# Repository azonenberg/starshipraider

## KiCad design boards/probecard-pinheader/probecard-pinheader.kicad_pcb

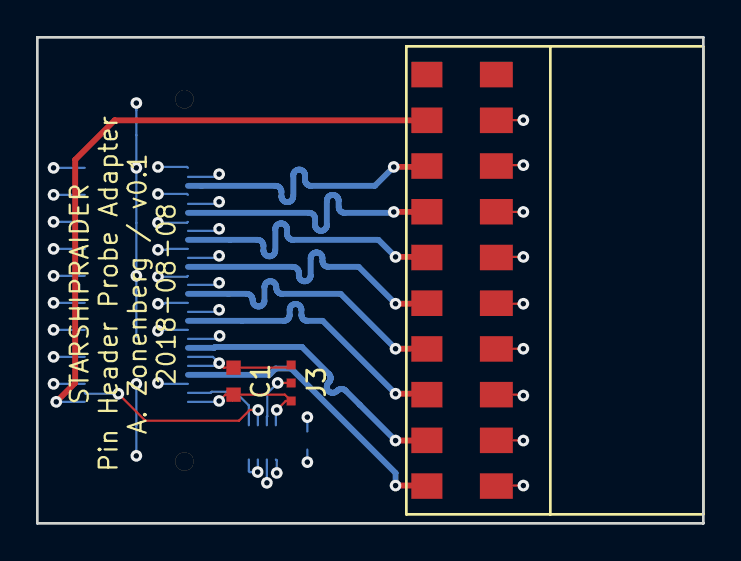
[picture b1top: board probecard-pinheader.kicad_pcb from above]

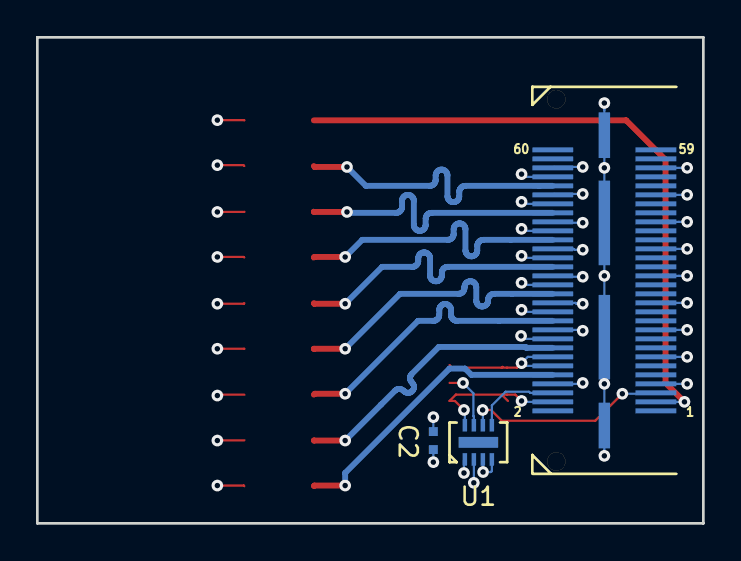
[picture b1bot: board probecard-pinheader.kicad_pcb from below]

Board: 4 copper layers, 37.0 x 27.0 mm, 6 parts (3 on the bottom side), 14 nets.

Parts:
C1: 4.7 uF; EIA_0603_CAP_NOSILK
C2: 0.47 uF; EIA_0402_CAP_NOSILK
J1: STARSHIPRAIDER_PROBE_MODULE; CONN_SAMTEC_QSH-030-01-L-D-A
J2: STARSHIPRAIDER_PINHDR; CONN_SAMTEC_SMH_110_02_L_D
J3: JUMPER_0402_SPDT; EIA_0402_JUMPER
U1: 24C04-DFN8; DFN_8_0.5MM_2x3MM

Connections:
/3V3: C1.1, C2.1, J1.4, J3.1, U1.2, U1.8
/DQ0: J1.10, J2.1
/DQ1: J1.16, J2.3
/DQ2: J1.22, J2.5
/DQ3: J1.28, J2.7
/DQ4: J1.34, J2.9
/DQ5: J1.40, J2.11
/DQ6: J1.46, J2.13
/DQ7: J1.52, J2.15
/EEPROM_WP_N: J3.2, U1.7
/GND: C1.2, C2.2, J1.7, J1.8, J1.12, J1.13, J1.14, J1.18, J1.19, J1.20, J1.24, J1.25, J1.26, J1.30, J1.31, J1.32, J1.36, J1.37, J1.38, J1.42, J1.43, J1.44, J1.48, J1.49, J1.50, J1.54, J1.55, J1.56, J1.GND, J2.2, J2.4, J2.6, J2.8, J2.10, J2.12, J2.14, J2.16, J2.18, J3.3, U1.1, U1.3, U1.4
/I2C_SCL: J1.5, U1.6
/I2C_SDA: J1.6, U1.5
/VCCO_REF: J1.3, J2.17

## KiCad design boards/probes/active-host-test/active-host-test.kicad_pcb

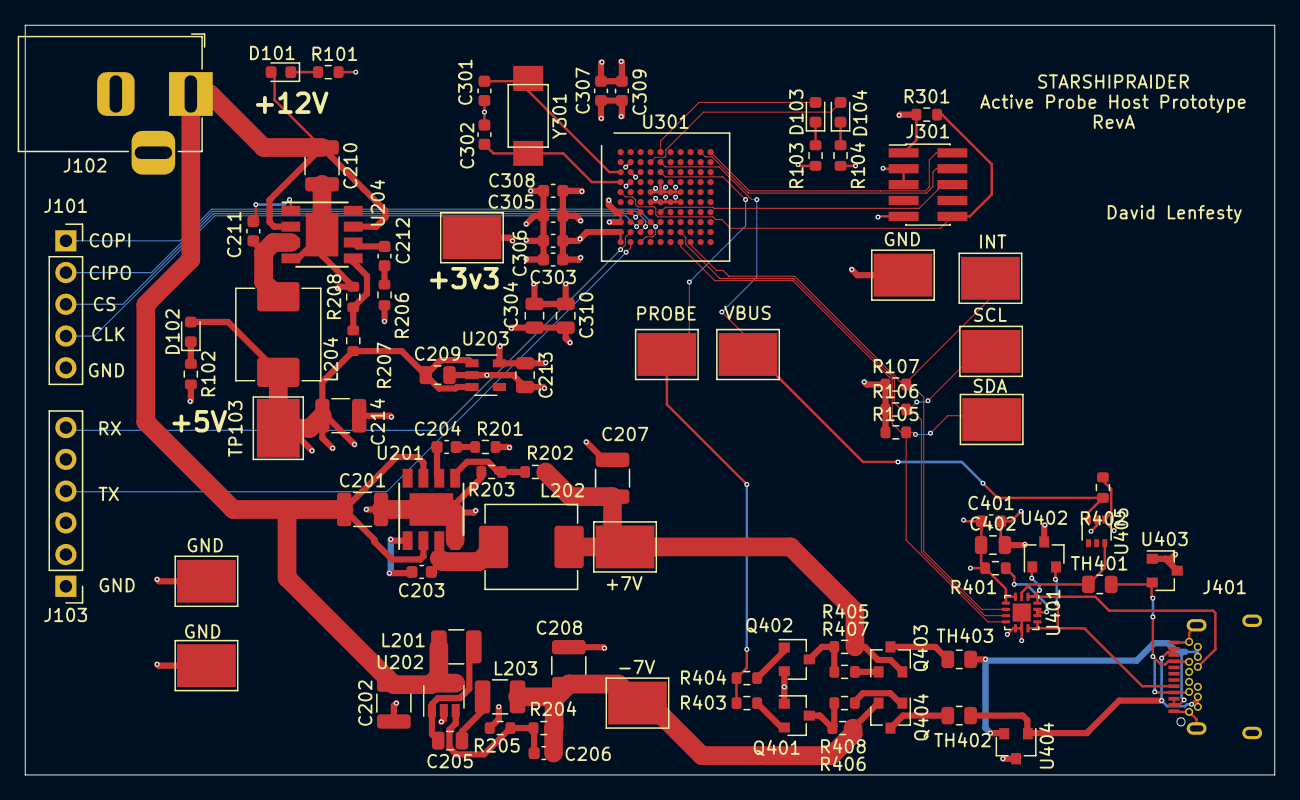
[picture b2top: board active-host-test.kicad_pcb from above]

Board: 4 copper layers, 100.0 x 60.0 mm, 93 parts (0 on the bottom side), 57 nets.

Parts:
C201, C202, C208, C210: 22u; C_1210_3225Metric
C203, C211, C306: 10n; C_0603_1608Metric
C204, C212: 6n8; C_0603_1608Metric
C205, C209, C213, C304, C310, C402: 1u; C_0805_2012Metric
C206: 330p; C_0603_1608Metric
C207, C214: 47u; C_1210_3225Metric
C301, C302: 10p; C_0603_1608Metric
C303, C305, C307, C308, C309, C401: 0u1; C_0603_1608Metric
D101, D102, D103, D104: LED; LED_0603_1608Metric
J101: Conn_01x05_Male; PinSocket_1x05_P2.54mm_Vertical
J102: Barrel_Jack; BarrelJack_Horizontal
J103: Conn_01x06_Male; PinHeader_1x06_P2.54mm_Vertical
J301: Conn_ARM_JTAG_SWD_10; PinHeader_2x05_P1.27mm_Vertical_SMD
J401: USB_C_Receptacle; 10137062
L201, L203: 22u; L_1210_3225Metric
L202, L204: 12u; L_Abracon_ASPI-0630LR
Q401: Q_PNP_BEC; SOT-23
Q402: Q_NPN_BEC; SOT-23
Q403: Q_PMOS_GSD; SOT-23
Q404: Q_NMOS_GSD; SOT-23
R101, R102, R105, R106, R107, R203, R205, R208, R301, R402, R403, R404, R405, R406: 10k; R_0603_1608Metric
R103, R104: 1k; R_0603_1608Metric
R201, R206: 6k8; R_0603_1608Metric
R202: 66k; R_0603_1608Metric
R204: 47k; R_0603_1608Metric
R207: 44k; R_0603_1608Metric
R401: 0R; R_0603_1608Metric
R407, R408: 100R; R_0603_1608Metric
TH401, TH402, TH403: Thermistor_PTC; R_0805_2012Metric
TP101, TP102, TP103, TP104, TP105, TP106, TP107, TP108, TP109, TP110, TP111, TP112: TestPoint; Keystone_5016
U201, U204: AP6502; Diodes_SO-8EP
U202: LM2611xMF; SOT-23-5
U203: AP2112K-3.3; SOT-23-5
U301: STM32F103V8Hx; LFBGA-100_10x10mm_Layout10x10_P0.8mm
U401: FUSB302BMPX; WQFN-14-1EP_2.5x2.5mm_P0.5mm_EP1.45x1.45mm
U402: STS232033B102; SOT-23
U403: STS232050B751; SOT-23
U404: STS232120B301; SOT-23
U405: LM66100; SOT-363_SC-70-6
Y301: 8MHz; Crystal_NX5032

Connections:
+3V3: C213.1, C303.1, C304.1, C305.1, C306.1, C307.1, C308.1, C309.1, C310.1, J301.1, R105.1, R106.1, R107.1, R301.1, TP104.1, U203.5, U301.B2, U301.D2, U301.F4, U301.F5, U301.F6, U301.F7, U301.J1, U301.K1
+5V: C209.1, C214.1, C401.1, C402.1, D102.2, L204.2, R207.1, R401.1, R402.1, TP103.1, U203.1, U203.3, U401.3, U401.4, U405.1
/+7V: C207.1, L202.2, Q403.2, R202.1, R405.1, TP101.1
/+12V: C201.1, C202.1, C210.1, D101.2, J102.1, L201.1, U201.2, U201.7, U202.4, U202.5, U204.2, U204.7
/-7V: C206.1, C208.1, L203.2, Q404.2, R204.1, R406.2, TP102.1
/I2C_SCL: R106.2, TP108.1, U301.J7, U401.6
/I2C_SDA: R105.2, TP107.1, U301.K7, U401.7
/I2C_~INT: R107.2, TP109.1, U301.K8, U401.5
/MCU/NRST: J301.10, R301.2, U301.E1
/MCU/SWCLK: J301.4, U301.A9
/MCU/SWDIO: J301.2, U301.A10
/MCU/SWO: J301.6, U301.G5
/MCU/UART_RX: J103.4, U301.K2
/MCU/UART_TX: J103.6, U301.J2
/PROBE_PWR_EN: R403.2, R404.2, TP105.1, U301.C5
/PROBE_VBUS_~EN: R402.2, TP106.1, U301.B5, U405.3
/SPI_CIPO: J101.2, U301.J3
/SPI_CLK: J101.4, U301.H3
/SPI_COPI: J101.1, U301.K3
/SPI_~CS: J101.3, U301.G3
/USB C/+7V_FUSED: J401.A2, J401.A3, J401.B2, J401.B3, TH403.1, U404.2
/USB C/+7V_GATED: Q403.3, TH403.2
/USB C/-7V_FUSED: J401.A10, J401.A11, J401.B10, J401.B11, TH402.2, U404.1
/USB C/-7V_GATED: Q404.3, TH402.1
/USB C/CC1: J401.A5, U401.10, U401.11, U402.2
/USB C/CC2: J401.B5, U401.1, U401.14, U402.1
/USB C/VBUS: TH401.1, U401.2, U405.6
/USB C/VBUS_FUSED: J401.A4, J401.A9, J401.B4, J401.B9, TH401.2, U403.2
/USRLED1: D103.2, U301.A5
/USRLED2: D104.2, U301.B4
GND: C201.2, C202.2, C207.2, C208.2, C209.2, C210.2, C213.2, C214.2, C301.2, C302.2, C303.2, C304.2, C305.2, C306.2, C307.2, C308.2, C309.2, C310.2, C401.2, C402.2, J101.5, J102.2, J103.1, J301.3, J301.5, J301.9, J401.A1, J401.A12, J401.B1, J401.B12, J401.S1, Q401.1, Q402.2, R101.2, R102.2, R103.2, R104.2, R201.2, R203.2, R205.2, R206.2, R208.2, TP110.1, TP111.1, TP112.1, U201.4, U201.9, U202.2, U203.2, U204.4, U204.9, U301.C2, U301.D5, U301.E4, U301.E5, U301.E6, U301.E7, U301.G1, U301.H1, U401.8, U401.9, U401.15, U402.3, U403.1, U403.3, U404.3, U405.2
unnamed: C203.1, U201.1
unnamed: C203.2, L202.1, U201.3
unnamed: C204.1, U201.6
unnamed: C204.2, R201.1
unnamed: C205.1, L203.1
unnamed: C205.2, L201.2, U202.1
unnamed: C206.2, R204.2, R205.1, U202.3
unnamed: C211.1, U204.1
unnamed: C211.2, L204.1, U204.3
unnamed: C212.1, U204.6
unnamed: C212.2, R206.1
unnamed: C301.1, U301.C1, Y301.1
unnamed: C302.1, U301.D1, Y301.2
unnamed: D101.1, R101.1
unnamed: D102.1, R102.1
unnamed: D103.1, R103.1
unnamed: D104.1, R104.1
unnamed: Q401.2, R403.1
unnamed: Q401.3, R406.1, R408.2
unnamed: Q402.1, R404.1
unnamed: Q402.3, R405.2, R407.2
unnamed: Q403.1, R407.1
unnamed: Q404.1, R408.1
unnamed: R202.2, R203.1, U201.5
unnamed: R207.2, R208.1, U204.5
unnamed: R401.2, U401.12, U401.13

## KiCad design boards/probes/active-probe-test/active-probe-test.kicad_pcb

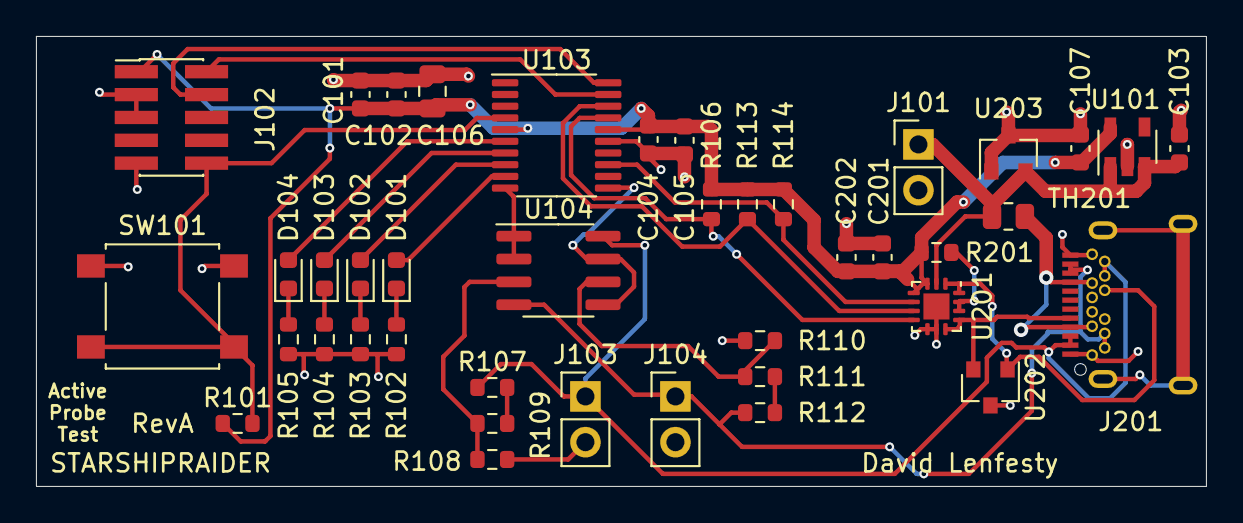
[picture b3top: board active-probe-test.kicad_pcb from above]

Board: 2 copper layers, 65.0 x 25.0 mm, 41 parts (0 on the bottom side), 29 nets.

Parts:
C101, C103, C104, C107, C201: 0u1; C_0603_1608Metric
C102: 10n; C_0603_1608Metric
C105, C202: 1u; C_0603_1608Metric
C106: 4u7; C_0805_2012Metric
D101, D102, D103, D104: LED; LED_0603_1608Metric
J101, J103, J104: Conn_01x02_Male; PinHeader_1x02_P2.54mm_Vertical
J102: Conn_ARM_JTAG_SWD_10; PinHeader_2x05_P1.27mm_Vertical_SMD
J201: USB_C_Receptacle; 10137062
R101, R106, R107, R108, R109, R110, R111, R112, R113, R114: 10k; R_0603_1608Metric
R102, R103, R104, R105: 1k; R_0603_1608Metric
R201: 0R; R_0603_1608Metric
SW101: SW_Push; SW_SPST_B3S-1000
TH201: Thermistor_PTC; R_0805_2012Metric
U101: AP2112K-3.3; SOT-23-5
U103: STM32F042F6Px; TSSOP-20_4.4x6.5mm_P0.65mm
U104: LM358; SOIC-8_3.9x4.9mm_P1.27mm
U201: FUSB302BMPX; WQFN-14-1EP_2.5x2.5mm_P0.5mm_EP1.45x1.45mm
U202: STS232033B102; SOT-23
U203: STS232050B751; SOT-23

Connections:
+3V3: C101.1, C102.1, C104.1, C105.1, C106.1, C107.1, C201.1, C202.1, J102.1, R101.1, R106.1, R113.1, R114.1, R201.1, U101.5, U103.5, U103.16, U201.3, U201.4
/+7V: J103.1, J201.A2, J201.A3, J201.B2, J201.B3, R107.1, U104.8
/+7V_SENSE: U103.10, U104.1, U104.2
/-7V: J104.1, J201.A10, J201.A11, J201.B10, J201.B11, R112.2, U104.4
/-7V_SENSE: U103.11, U104.5, U104.7
/FUSB_INT: R114.2, U103.13, U201.5
/I2C1_SCL: R106.2, U103.17, U201.7
/I2C1_SDA: R113.2, U103.18, U201.6
/NRST: J102.10, R101.2, SW101.2, U103.4
/SWCLK: J102.4, U103.20
/SWDIO: J102.2, U103.19
/USB/CC1: J201.A5, U201.10, U201.11, U202.2
/USB/CC2: J201.B5, U201.1, U201.14, U202.1
/USB/VBUS_RAW: J201.A4, J201.A9, J201.B4, J201.B9, TH201.2
/USRLED1: D104.2, U103.6
/USRLED2: D103.2, U103.7
/USRLED3: D102.2, U103.8
/USRLED4: D101.2, U103.9
/VBUS: C103.1, J101.1, TH201.1, U101.1, U101.3, U201.2, U203.2
GND: C101.2, C102.2, C103.2, C104.2, C105.2, C106.2, C107.2, C201.2, C202.2, J101.2, J102.3, J102.5, J102.9, J103.2, J104.2, J201.A1, J201.A12, J201.B1, J201.B12, R102.2, R103.2, R104.2, R105.2, R109.2, R110.1, SW101.1, U101.2, U103.15, U201.8, U201.9, U201.15, U202.3, U203.1, U203.3
unnamed: D101.1, R102.1
unnamed: D102.1, R103.1
unnamed: D103.1, R104.1
unnamed: D104.1, R105.1
unnamed: R107.2, R108.1
unnamed: R108.2, R109.1, U104.3
unnamed: R110.2, R111.1, U104.6
unnamed: R111.2, R112.1
unnamed: R201.2, U201.12, U201.13

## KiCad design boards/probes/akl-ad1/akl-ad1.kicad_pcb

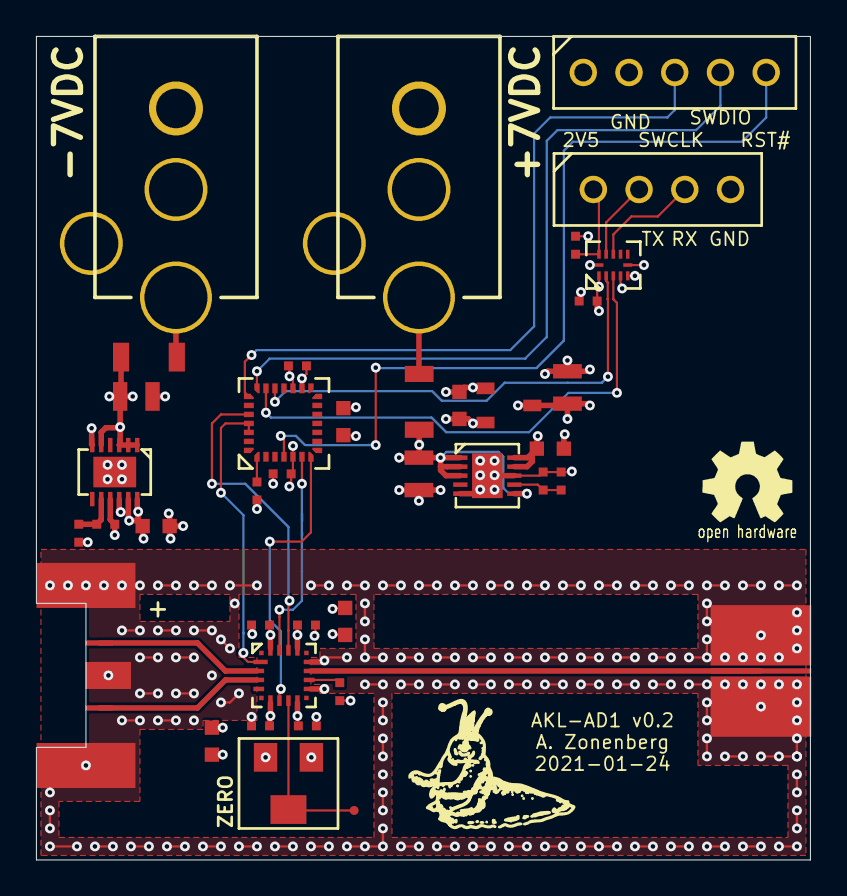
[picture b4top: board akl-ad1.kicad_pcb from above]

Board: 4 copper layers, 43.0 x 45.8 mm, 39 parts (0 on the bottom side), 28 nets.

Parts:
C3, C4, C14, C15, C16, C17: 4.7 uF; EIA_0603_CAP_NOSILK
C5, C6, C7, C8, C12, C13, C18, C19, C20, C21: 0.47 uF; EIA_0402_CAP_NOSILK
C9, C10, C11: 4.7 uF 16V; EIA_0805_CAP_NOSILK
J1: 3211-60087; CONN_SMPM_DUAL_AMPHENOL_3211-60087
J2: 901-10511-3; CONN_SMA_EDGE_AMPHENOL_901_10511_3
J3: TESTPOINT; TESTPOINT_SMT_0.5MM
J4, J5: BARREL; CONN_CUI_PJ-058BH_HIPWR_BARREL_NOSLOT
J6: Conn_01x05; CONN_HEADER_2.54MM_1x5
J7: Conn_01x04; CONN_HEADER_2.54MM_1x4
L1, L2: BLM31KN271SH1L; EIA_1206_CAP_NOSILK
R1: 49.9; EIA_0402_RES_NOSILK
R2, R3: 24.9K; EIA_0402_CAP_NOSILK
R4: 10K; EIA_0402_RES_NOSILK
RV1: SM-43TW103; TRIMPOT_NIDEC_SM4xW
U1: LMH6401; QFN_16_0.5MM_3x3MM_TI_RMZ
U2: LT3042; DFN_10_0.5MM_3x3MM
U3: LT3093; DFN_12_0.5MM_3x3MM
U4: MCP1703T-2502E/CB; SOT23_3
U5: STM32F031-QFN28; QFN_28_0.5MM_4x4MM_NOPAD
U6: TXB0104RUT; QFN_12_0.4MM_2x1.7MM_TI_RUT

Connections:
/2V5_D: C16.1, C17.1, C18.1, C19.1, C21.1, J6.1, U4.2, U5.5, U5.17, U6.1, U6.12
/2V5_N: C4.2, C6.2, C8.2, C15.1, RV1.3, U1.5, U1.16, U3.10, U3.11, U3.12
/2V5_P: C3.1, C5.1, C7.1, C14.1, RV1.1, U1.8, U1.13, U2.9, U2.10
/AMP_CS_N: U1.15, U5.6
/AMP_PD: U1.6, U5.7
/GND: C3.2, C4.1, C5.2, C6.1, C7.2, C8.1, C9.2, C10.2, C11.2, C12.2, C13.2, C14.2, C15.2, C16.2, C17.2, C18.2, C19.2, C20.2, C21.2, J1.3, J2.2, J4.2, J5.2, J6.2, J7.4, R1.2, R2.2, R3.2, R4.2, U1.9, U1.12, U2.5, U2.8, U2.PAD, U3.6, U3.9, U4.1, U5.16, U6.4, U6.5, U6.6
/IN_N: J1.2, U1.3
/IN_P: J1.1, U1.2
/MCU/MCU_RST_N: J6.5, U5.4
/MCU/SWCLK: J6.3, U5.22
/MCU/SWDIO: J6.4, U5.21
/MCU/UART_RX: U5.20, U6.3
/MCU/UART_RX_VOUT: J7.3, U6.9
/MCU/UART_TX: U5.19, U6.2
/MCU/UART_TX_VOUT: J7.2, U6.10
/MCU/VCCIO_UART: C20.1, J7.1, U6.11
/Power Supply/7V0_N: C10.1, L2.1, U3.1, U3.2, U3.3, U3.5, U3.PAD
/Power Supply/7V0_P: C9.1, C11.1, L1.1, U2.1, U2.2, U2.3, U2.6, U4.3
/SPI_SCK: U1.14, U5.24
/SPI_SDIO: U1.1, U5.25, U5.26
/VOCM: J3.1, RV1.2, U1.7
/VOUT: J2.1, U1.11
unnamed: C12.1, R2.1, U2.7
unnamed: C13.1, R3.1, U3.8
unnamed: J4.1, L1.2
unnamed: J5.1, L2.2
unnamed: R1.1, U1.10
unnamed: R4.1, U5.1

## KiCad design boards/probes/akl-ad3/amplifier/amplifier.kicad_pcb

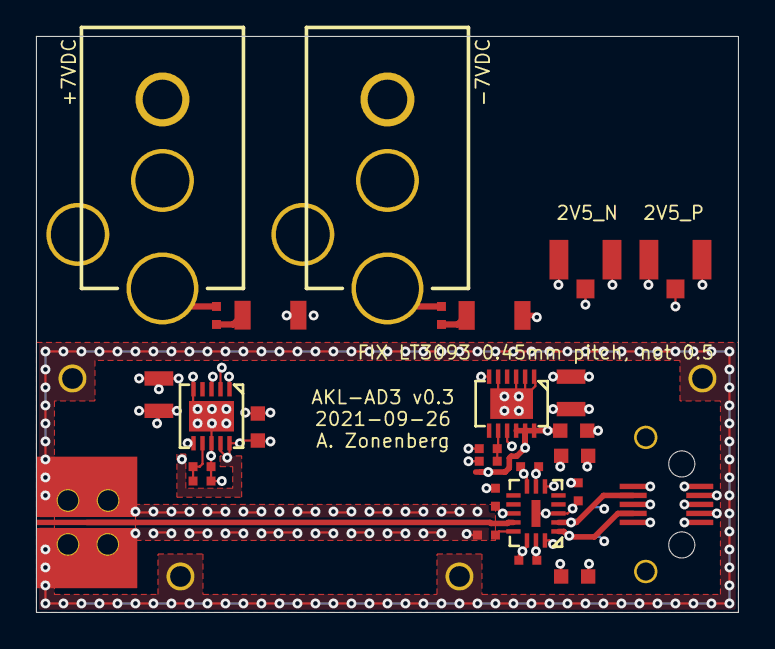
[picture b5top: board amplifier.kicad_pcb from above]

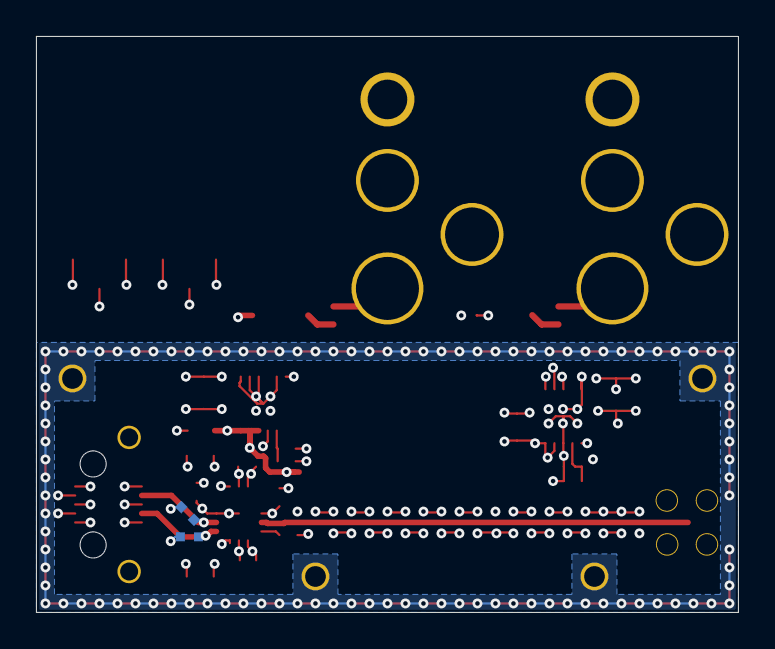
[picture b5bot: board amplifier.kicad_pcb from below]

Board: 4 copper layers, 39.0 x 32.0 mm, 34 parts (2 on the bottom side), 15 nets.

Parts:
C1, C2: 4.7 uF 16V; EIA_0805_CAP_NOSILK
C3, C4, C9, C10, C11, C12: 0.47 uF; EIA_0402_CAP_NOSILK
C5, C6, C7, C8: 4.7 uF; EIA_0603_CAP_NOSILK
F1, F2: 1A; EIA_0402_RES_NOSILK
J1, J2: CONN_3_PWROUT; CONN_CUI_PJ-058BH_HIPWR_BARREL_NOSLOT
J3: 901-10510-2; CONN_SMA_EDGE_AMPHENOL_901_10510-2
J4, J5: U.FL; CONN_U.FL_TE_1909763-1
J6: LSHM-105-02.5-L-DV-A-S-K-TR; CONN_SAMTEC_LSHM-105-02.5-L-DV-A-S-K-TR
L1, L2: BLM31KN271SH1L; EIA_1206_CAP_NOSILK
MH1, MH2, MH3, MH4: 1MM; MECHANICAL_CLEARANCEHOLE_M1
R1, R2: 24.9K; EIA_0402_RES_NOSILK
R3: 49.9; EIA_0402_RES_NOSILK
R4, R5: 110; EIA_0402_RES_NOSILK
U1: LT3042; DFN_10_0.5MM_3x3MM
U2: LT3093; DFN_12_0.5MM_3x3MM
U3: ADL5569; QFN_16_0.5MM_2.5x3MM

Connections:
/2V5_N: C6.1, C8.1, C10.1, C12.1, J5.1, U2.10, U2.11, U2.12, U3.3, U3.6, U3.11, U3.PAD
/2V5_P: C5.1, C7.1, C9.1, C11.1, J4.1, U1.9, U1.10, U3.8, U3.14, U3.16
/7V0_N: C2.1, L2.1, U2.1, U2.2, U2.3, U2.5, U2.PAD
/7V0_P: C1.1, L1.1, U1.1, U1.2, U1.3, U1.6
/GND: C1.2, C2.2, C3.2, C4.2, C5.2, C6.2, C7.2, C8.2, C9.2, C10.2, C11.2, C12.2, J1.2, J2.2, J3.2, J4.2, J5.2, J6.1, J6.2, J6.4, J6.5, J6.6, J6.8, J6.9, J6.10, J6.SHLD, MH1.1, MH2.1, MH3.1, MH4.1, R1.2, R2.2, R3.2, R4.2, R5.2, U1.5, U1.8, U1.PAD, U2.6, U2.9, U3.7, U3.15
/VIN_N: J6.3, R5.1, U3.1
/VIN_P: J6.7, R4.1, U3.2
/VOUT: J3.1, U3.12
unnamed: C3.1, R1.1, U1.7
unnamed: C4.1, R2.1, U2.8
unnamed: F1.1, J1.1
unnamed: F1.2, L1.2
unnamed: F2.1, J2.1
unnamed: F2.2, L2.2
unnamed: R3.1, U3.13

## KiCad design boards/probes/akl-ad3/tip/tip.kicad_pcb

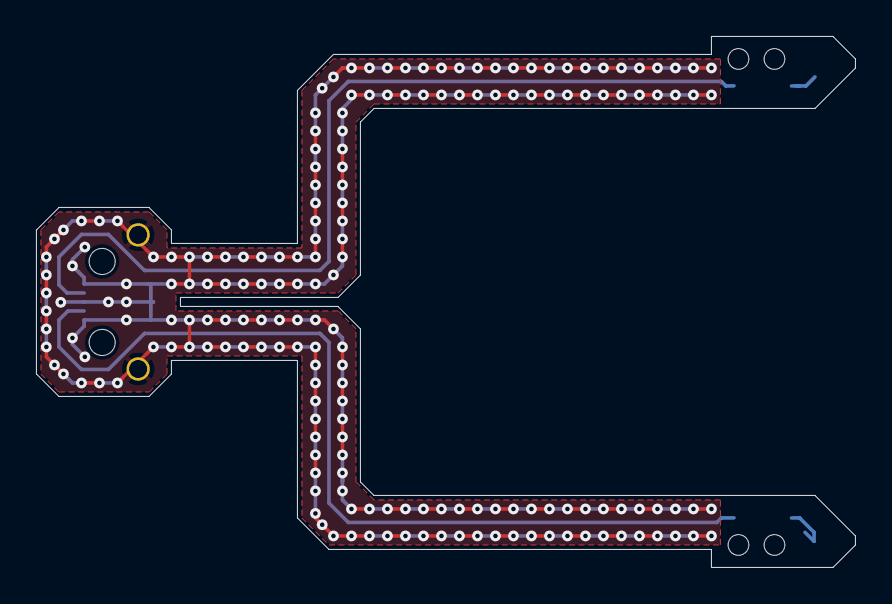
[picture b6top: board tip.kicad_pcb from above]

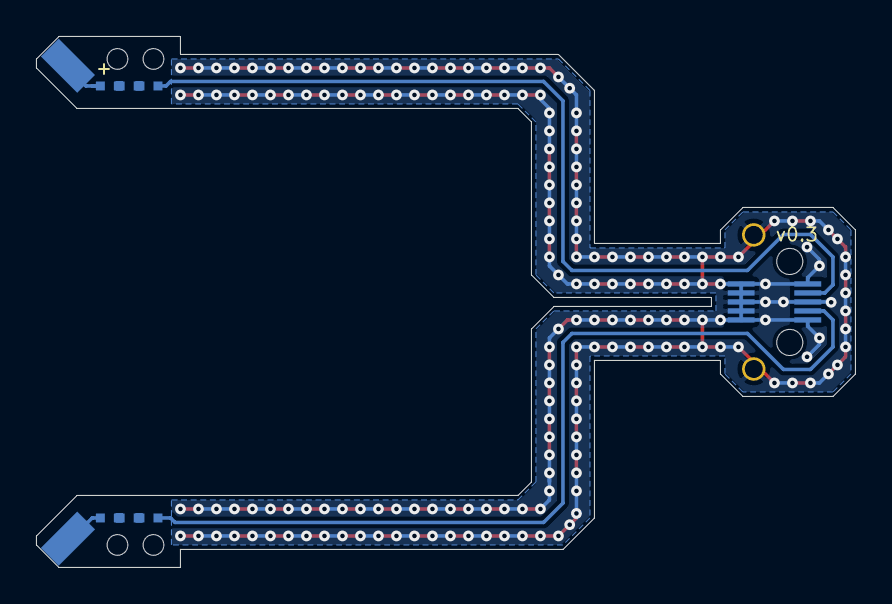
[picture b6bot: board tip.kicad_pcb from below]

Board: 2 copper layers, 45.5 x 29.5 mm, 9 parts (9 on the bottom side), 9 nets.

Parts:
J1: Conn_01x10_shielded; CONN_SAMTEC_LSHM-105-02.5-L-DV-A-S-K-TR
J2, J3: SOCKET; CONN_TE_2-331677-6_EDGELAUNCH
R1, R2: FC0402E50R0BTT0; EIA_0402_RES_NOSILK_FLIPCHIP
R3, R4, R5, R6: FC0402E2000BTT0; EIA_0402_RES_NOSILK_FLIPCHIP

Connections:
/GND: J1.1, J1.2, J1.3, J1.5, J1.6, J1.7, J1.9, J1.10, J1.SHLD
/IN_N: J3.1, R6.1
/IN_P: J2.1, R5.1
/IN_R_N: J1.4, R2.2
/IN_R_P: J1.8, R1.2
unnamed: R1.1, R3.2
unnamed: R2.1, R4.2
unnamed: R3.1, R5.2
unnamed: R4.1, R6.2

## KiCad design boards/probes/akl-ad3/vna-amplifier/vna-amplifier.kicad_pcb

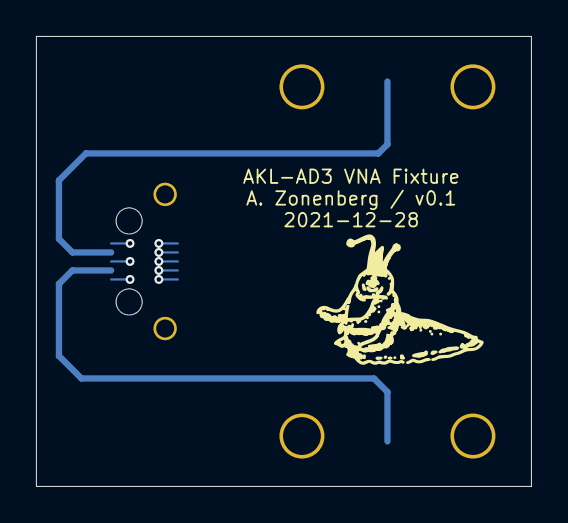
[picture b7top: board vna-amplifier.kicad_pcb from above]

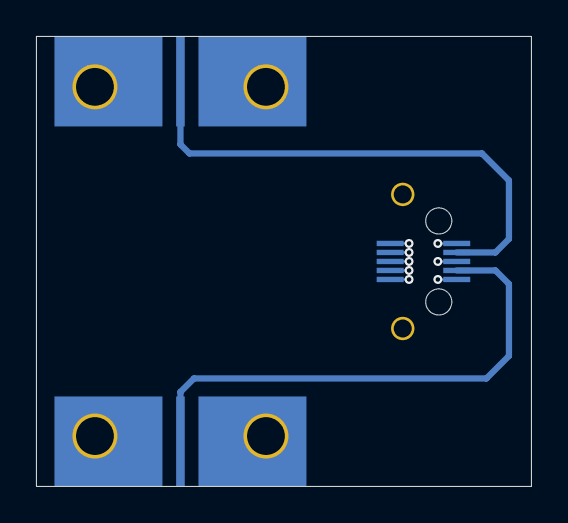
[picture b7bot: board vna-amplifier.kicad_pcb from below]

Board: 4 copper layers, 27.5 x 25.0 mm, 3 parts (3 on the bottom side), 3 nets.

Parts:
J1: Conn_01x10_shielded; CONN_SAMTEC_LSHM-105-02.5-L-DV-A-S-K-TR
J2, J3: 32K243-40ML5; CONN_SMA_EDGE_ROSENBERGER_32K243_40ML5

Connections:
/GND: J1.1, J1.2, J1.3, J1.5, J1.6, J1.7, J1.9, J1.10, J1.SHLD, J2.2, J3.2
/IN_R_N: J1.4, J2.1
/IN_R_P: J1.8, J3.1

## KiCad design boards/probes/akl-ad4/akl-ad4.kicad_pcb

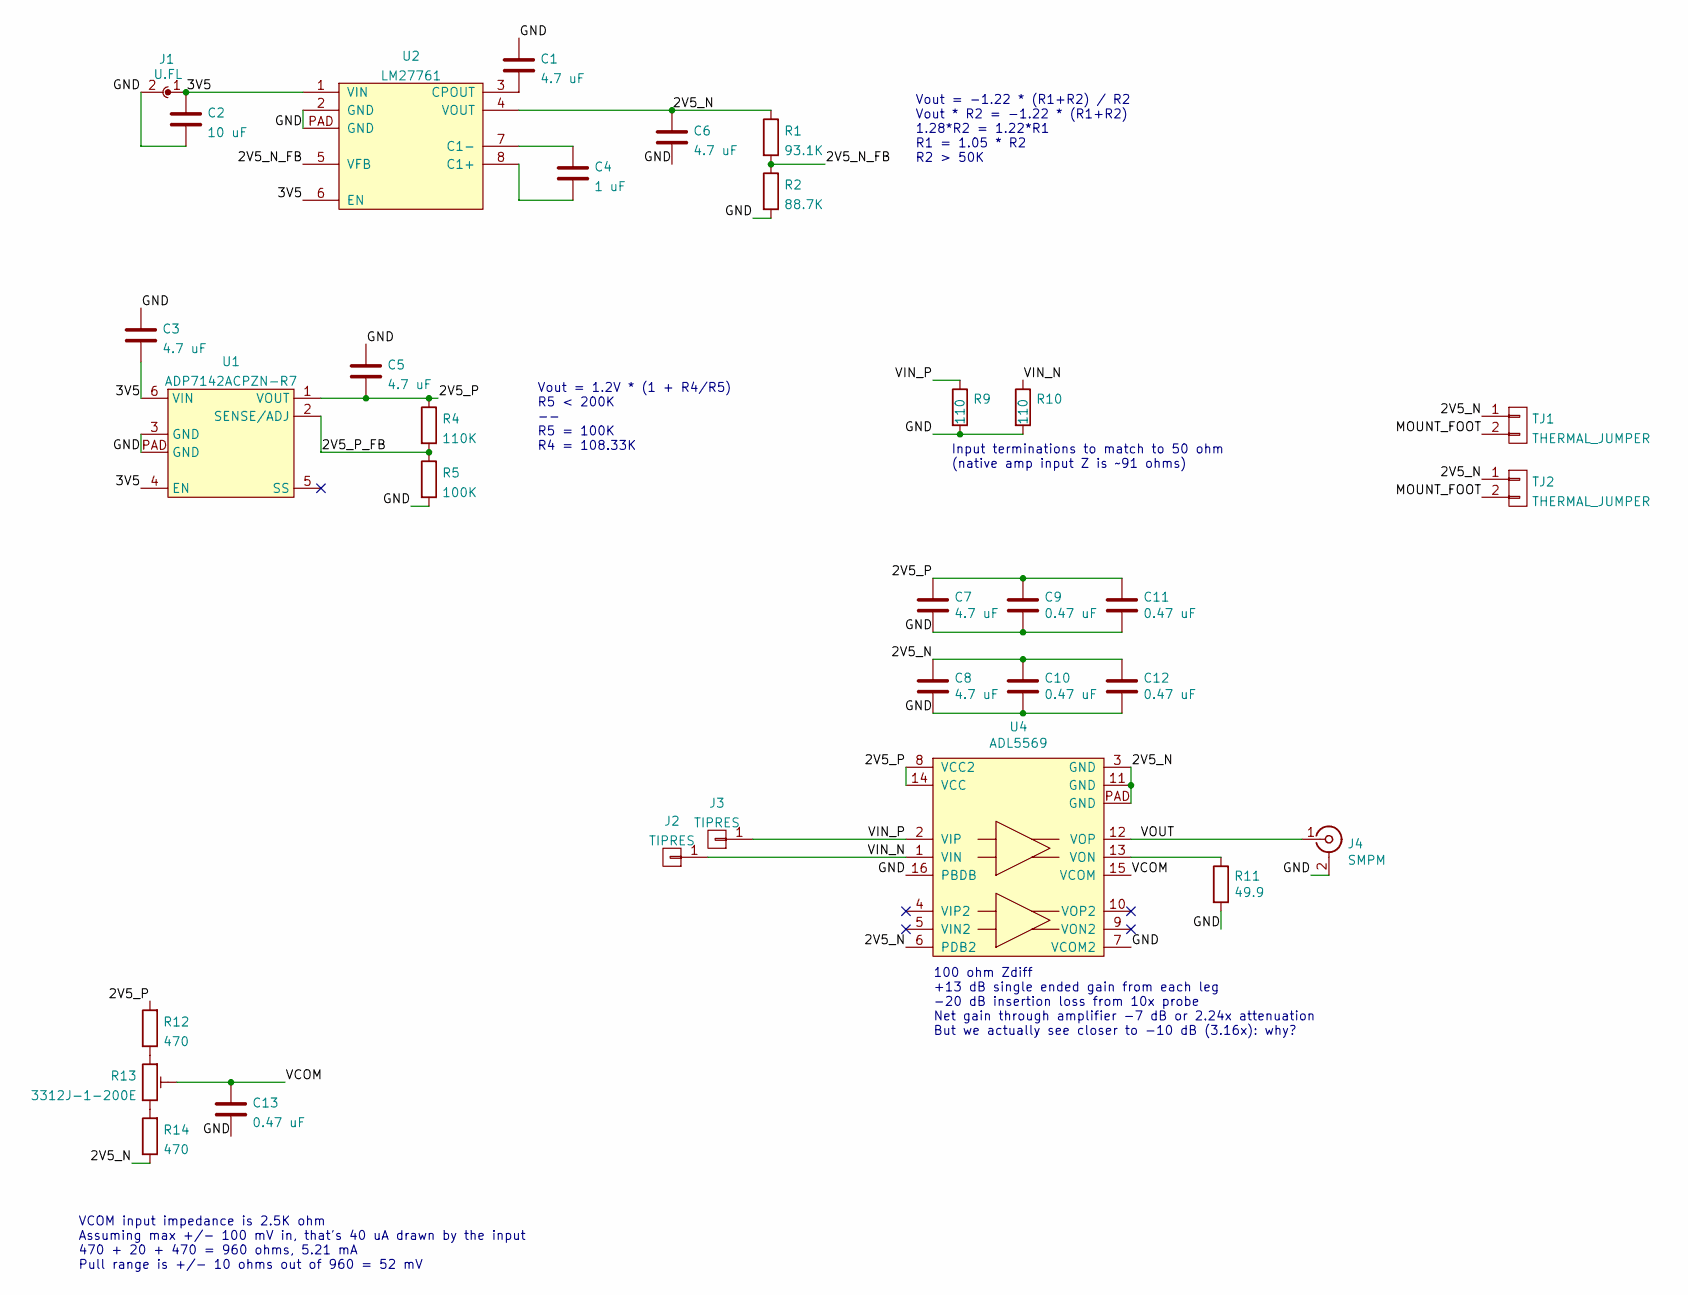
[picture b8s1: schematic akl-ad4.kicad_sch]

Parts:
C1, C3, C5, C6, C7, C8: 4.7 uF; EIA_0603_CAP_NOSILK
C2: 10 uF; EIA_0805_CAP_NOSILK
C4: 1 uF; EIA_0603_CAP_NOSILK
C9, C10, C11, C12, C13: 0.47 uF; EIA_0402_CAP_NOSILK
J1: U.FL; CONN_U.FL_TE_1909763-1
J2, J3: TIPRES; EDGELAUNCH_350UM
J4: SMPM; CONN_SMPM_AMPHENOL_925-169J-51PT_SHORT
R1: 93.1K; EIA_0402_RES_NOSILK
R2: 88.7K; EIA_0402_RES_NOSILK
R4: 110K; EIA_0402_RES_NOSILK
R5: 100K; EIA_0402_RES_NOSILK
R9, R10: 110; EIA_0402_RES_NOSILK
R11: 49.9; EIA_0402_RES_NOSILK
R12, R14: 470; EIA_0402_RES_NOSILK
R13: 3312J-1-200E; RES_TRIM_BOURNS_3312
TJ1, TJ2: THERMAL_JUMPER; EIA_0603_RES_NOSILK
U1: ADP7142ACPZN-R7; DFN_6_0.65MM_2x2MM
U2: LM27761; DFN_8_0.5MM_2x2MM
U4: ADL5569; QFN_16_0.5MM_2.5x3MM

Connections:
/2V5_N: C6.1, C8.1, C10.1, C12.1, R1.1, R14.1, TJ1.1, TJ2.1, U2.4 (VOUT), U4.3 (GND), U4.6 (PDB2), U4.11 (GND), U4.PAD (GND)
/2V5_N_FB: R1.2, R2.1, U2.5 (VFB)
/2V5_P: C5.2, C7.1, C9.1, C11.1, R4.1, R12.2, U1.1 (VOUT), U4.8 (VCC2), U4.14 (VCC)
/2V5_P_FB: R4.2, R5.1, U1.2 (SENSE/ADJ)
/3V5: C2.1, C3.2, J1.1, U1.4 (EN), U1.6 (VIN), U2.1 (VIN), U2.6 (EN)
/GND: C1.1, C2.2, C3.1, C5.1, C6.2, C7.2, C8.2, C9.2, C10.2, C11.2, C12.2, C13.2, J1.2, J4.2 (Ext), R2.2, R5.2, R9.2, R10.2, R11.2, U1.3 (GND), U1.PAD (GND), U2.2 (GND), U2.PAD (GND), U4.7 (VCOM2), U4.16 (PBDB)
/MOUNT_FOOT: TJ1.2, TJ2.2
/VCOM: C13.1, R13.2, U4.15 (VCOM)
/VIN_N: J2.1, R10.1, U4.1 (VIN)
/VIN_P: J3.1, R9.1, U4.2 (VIP)
/VOUT: J4.1 (In), U4.12 (VOP)
unnamed: C1.2, U2.3 (CPOUT)
unnamed: C4.1, U2.7 (C1-)
unnamed: C4.2, U2.8 (C1+)
unnamed: R11.1, U4.13 (VON)
unnamed: R12.1, R13.1
unnamed: R13.3, R14.2

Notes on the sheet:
Vout = 1.2V * (1 + R4/R5) R5 < 200K -- R5 = 100K R4 = 108.33K
VCOM input impedance is 2.5K ohm Assuming max +/- 100 mV in, that's 40 uA drawn by the input 470 + 20 + 470 = 960 ohms, 5.21 mA Pull range is +/- 10 ohms out of 960 = 52 mV
Input terminations to match to 50 ohm (native amp input Z is ~91 ohms)
Vout = -1.22 * (R1+R2) / R2 Vout * R2 = -1.22 * (R1+R2) 1.28*R2 = 1.22*R1 R1 = 1.05 * R2 R2 > 50K
100 ohm Zdiff +13 dB single ended gain from each leg -20 dB insertion loss from 10x probe Net gain through amplifier -7 dB or 2.24x attenuation But we actually see closer to -10 dB (3.16x): why?

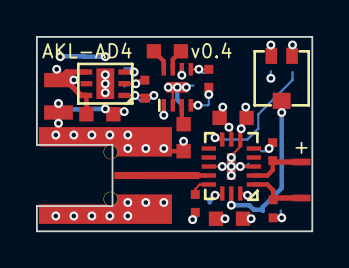
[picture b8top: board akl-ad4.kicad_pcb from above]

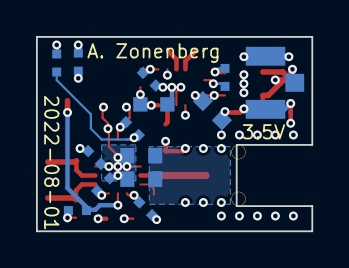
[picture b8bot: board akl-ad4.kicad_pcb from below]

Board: 4 copper layers, 15.3 x 10.8 mm, 32 parts (14 on the bottom side), 17 nets.
